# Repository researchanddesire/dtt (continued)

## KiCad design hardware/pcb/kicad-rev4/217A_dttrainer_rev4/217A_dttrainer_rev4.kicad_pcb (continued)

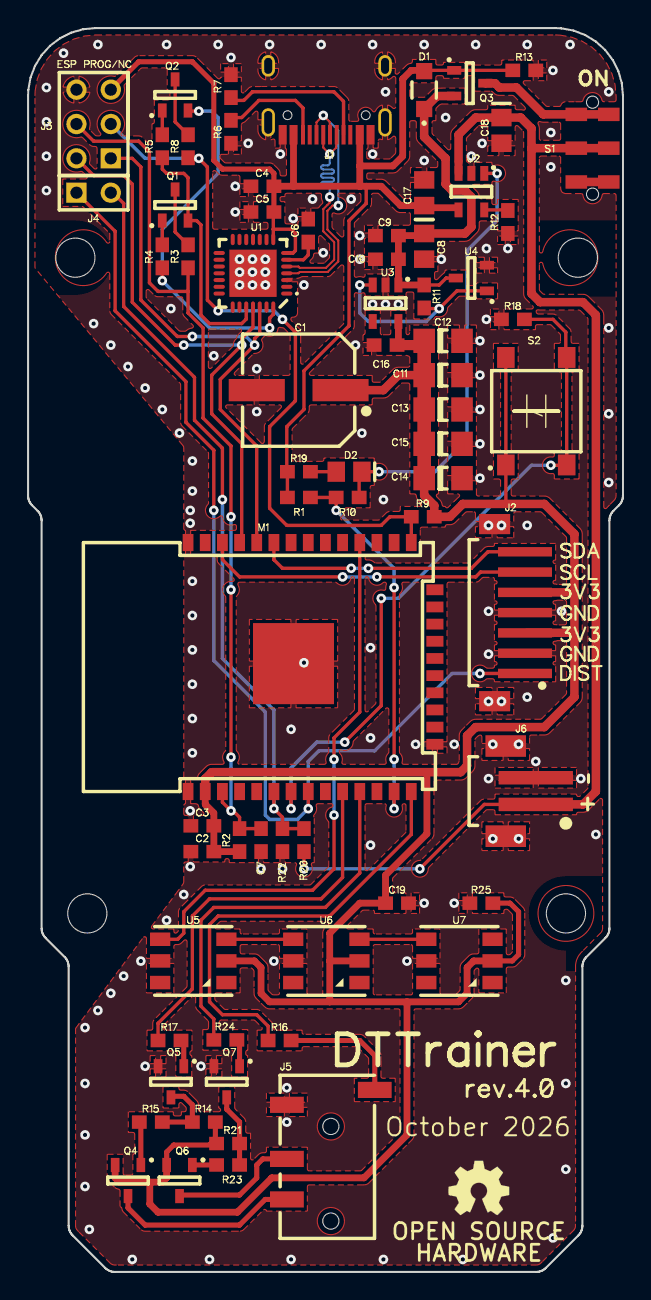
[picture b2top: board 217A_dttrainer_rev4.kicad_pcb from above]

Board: 2 copper layers, 44.0 x 92.0 mm, 74 parts (0 on the bottom side), 46 nets.

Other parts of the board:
@HOLE0: HOLE0
@HOLE1: HOLE1
@HOLE2: HOLE2
@HOLE3: HOLE3
LOGO1: OSHW-Logo_5.7x6mm_SilkScreen; OSHW_Logo

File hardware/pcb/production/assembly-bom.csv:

Comment,Designator,Footprint,LCSC Part #,Quantity
10uF,C2,217A_dttrainer_rev4:C2,C237435,1
100nF,C3,217A_dttrainer_rev4:C3,C519438,1
1uF,"C4,C9,C16,C19","217A_dttrainer_rev4:C4,217A_dttrainer_rev4:C9,217A_dttrainer_rev4:C16,217A_dttrainer_rev4:C19",C106248,4
100nF,"C5,C6,C10","217A_dttrainer_rev4:C5,217A_dttrainer_rev4:C6,217A_dttrainer_rev4:C10",C108079,3
10uF,C7,217A_dttrainer_rev4:C7,C109457,1
10uF,"C8,C17,C18","217A_dttrainer_rev4:C8,217A_dttrainer_rev4:C17,217A_dttrainer_rev4:C18",C89827,3
100uF,"C11,C12,C13,C14,C15","217A_dttrainer_rev4:C11,217A_dttrainer_rev4:C12,217A_dttrainer_rev4:C13,217A_dttrainer_rev4:C14,217A_dttrainer_rev4:C15",C15008,5
B5819W,D1,217A_dttrainer_rev4:D1,C22463588,1
CHARGE,D2,217A_dttrainer_rev4:D2,C94868,1
TYPE-C-31-M-12,J1,217A_dttrainer_rev4:J1,C165948,1
HC-ZH-7PLT,J2,217A_dttrainer_rev4:J2,HC-ZH-7PLT,1
3.5mm Jack,J5,217A_dttrainer_rev4:J5,C431535,1
LiPo,J6,217A_dttrainer_rev4:J6,C2763702,1
ESP32-WROOM-32D,M1,217A_dttrainer_rev4:M1,C701343,1
BC817,"Q1,Q2,Q5,Q7","217A_dttrainer_rev4:Q1,217A_dttrainer_rev4:Q2,217A_dttrainer_rev4:Q5,217A_dttrainer_rev4:Q7",C8658,4
Si2301,Q3,217A_dttrainer_rev4:Q3,C727151,1
MMBT4403,"Q4,Q6","217A_dttrainer_rev4:Q4,217A_dttrainer_rev4:Q6",C78864,2
1K,"R1,R15,R17,R23,R24,R25","217A_dttrainer_rev4:R1,217A_dttrainer_rev4:R15,217A_dttrainer_rev4:R17,217A_dttrainer_rev4:R23,217A_dttrainer_rev4:R24,217A_dttrainer_rev4:R25",C14676,6
10K,"R2,R4,R5,R9,R11,R13,R14,R18,R21","217A_dttrainer_rev4:R2,217A_dttrainer_rev4:R4,217A_dttrainer_rev4:R5,217A_dttrainer_rev4:R9,217A_dttrainer_rev4:R11,217A_dttrainer_rev4:R13,217A_dttrainer_rev4:R14,217A_dttrainer_rev4:R18,217A_dttrainer_rev4:R21",C99198,9
100R,"R3,R8","217A_dttrainer_rev4:R3,217A_dttrainer_rev4:R8",C110091,2
5.1K,"R6,R7","217A_dttrainer_rev4:R6,217A_dttrainer_rev4:R7",C105580,2
2K,"R12,R19","217A_dttrainer_rev4:R12,217A_dttrainer_rev4:R19",C105581,2
300R,R16,217A_dttrainer_rev4:R16,C137637,1
100K,"R20,R22","217A_dttrainer_rev4:R20,217A_dttrainer_rev4:R22",C14675,2
JS102011JAQN,S1,217A_dttrainer_rev4:S1,C221658,1
WAKE,S2,217A_dttrainer_rev4:S2,C381038,1
CP2102,U1,217A_dttrainer_rev4:U1,C6568,1
TP4054,U2,217A_dttrainer_rev4:U2,C32574,1
ME6211C33,U3,217A_dttrainer_rev4:U3,C82942,1
WS2813 / C5359034,"U5,U6,U7","217A_dttrainer_rev4:U5,217A_dttrainer_rev4:U6,217A_dttrainer_rev4:U7",C5359034,3
